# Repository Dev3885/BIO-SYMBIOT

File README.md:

# BIO SYMBIOT

**Bio-Resonant IoT Framework for Precision Microclimate Stabilization and Human-Plant Symbiosis**

An advanced IoT system that monitors and optimizes plant microclimates while mathematically quantifying the symbiotic relationship between tree biological resonance and human limbic well-being in a shared environment for regulation of the same towards overall health and tranquility.

---

Abstract

Inspired by research into plant communication networks, this project treats flora as an active, measurable node in a shared microclimate. We have built a mathematical proxy layer on top of real sensor data to test whether plant-state and human-comfort signals move together in a meaningful and mathematically honest way, proving that plants and humans react similarly in a given microclimate. And the results are amazing, we've achieved a **89.23%** of correlation between the plant's health and human limbic profile, when subjected to the exact same environment, with an alignment rate of **0.796**; which means that there is a 80% chance of predicting one variable, given the other variable. 
Next the project goes onto make use of this data to create a empathetic relationship between trees and humans. We have done that through actuation. 

The system validates a novel dual-bridge asymmetric weighting model for bio-symbiosis research, inspired by Peter Wohlleben’s **The Hidden Life of Trees**.

---

##  Key Features

- **Real-time Autonomous Irrigation** with manual override + 1-minute auto-timeout
- **Multi-sensor Microclimate Monitoring** (Soil Moisture, Ambient Light, Air Quality)
- **Local + Cloud Telemetry** (OLED display + Blynk IoT)
- **Advanced Noise Suppression** using FFT in MATLAB
- **Bio-Symbiosis Analytics** with Pearson correlation & linear regression (R² = 0.7962)
- **Robust Hardware Design** with optocoupler isolation, flyback diode, and star-ground topology
- **Professional PCB** designed in KiCad

---

##  Tech Stack

### Hardware
- **Microcontroller**: NodeMCU ESP8266
- **Sensors**: Capacitive Soil Moisture, BH1750 (Light), MQ-135 (Air Quality)
- **Display**: SSD1306 OLED (I2C)
- **Actuators**: 5V Relay + DC Water Pump
- **PCB**: Custom design in KiCad

### Software
- **Firmware**: Arduino (C++) with Blynk, non-blocking FSM
- **Analytics**: MATLAB (Serial parsing, FFT, regression, Shannon Entropy)
- **EDA**: KiCad

---

##  Results

- **Human-Tree Resonance Correlation**: **89.23%**
- **Predictive Model R²**: **0.7962**
- **System Stability Score** (Shannon Entropy): **27.94%**
- Successfully suppressed EMI and voltage sag issues
- Demonstrated clear asymmetric divergence validating the dual-bridge proxy model

---

##  Project Structure

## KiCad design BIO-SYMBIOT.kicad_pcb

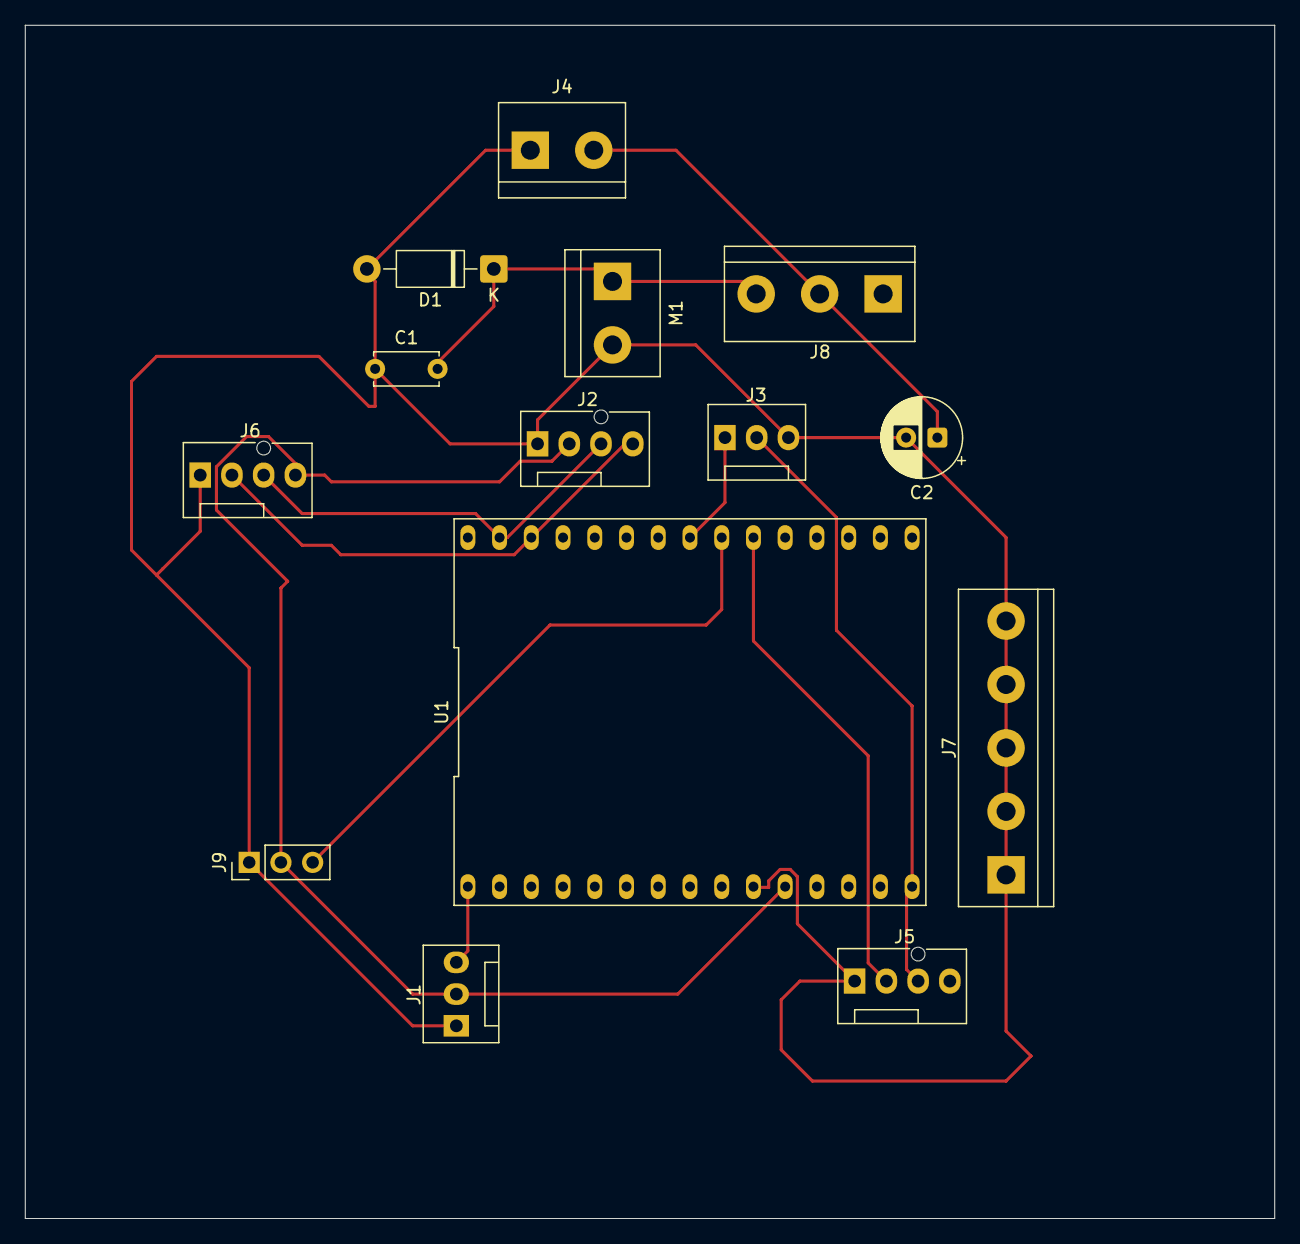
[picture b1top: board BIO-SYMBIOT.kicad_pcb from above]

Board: 2 copper layers, 100.0 x 95.5 mm, 14 parts (0 on the bottom side), 11 nets.

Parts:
C1: 0.1µF; C_Disc_D5.0mm_W2.5mm_P5.00mm
C2: 100µF; CP_Radial_D6.3mm_P2.50mm
D1: 1N4007; D_DO-41_SOD81_P10.16mm_Horizontal
J1: Soil Moisture Sensor; FanPinHeader_1x03_P2.54mm_Vertical
J2: SSD1306 OLED; FanPinHeader_1x04_P2.54mm_Vertical
J3: Rellay Module; FanPinHeader_1x03_P2.54mm_Vertical
J4: 5V Power Input; TerminalBlock_bornier-2_P5.08mm
J5: MQ135 Gas Sensor; FanPinHeader_1x04_P2.54mm_Vertical
J6: BH1750_LIGHT; FanPinHeader_1x04_P2.54mm_Vertical
J7: Screw_Terminal_01x05; TerminalBlock_bornier-5_P5.08mm
J8: Relay_Switch_Pins; TerminalBlock_bornier-3_P5.08mm
J9: TTP223 Touch Switch Module; PinHeader_1x03_P2.54mm_Vertical
M1: 5V Motor; TerminalBlock_bornier-2_P5.08mm
U1: NodeMCU1.0(ESP-12E); NodeMCU_LoLin_V3_Custom

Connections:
/5V: J3.2, J5.3, U1.15 (VIN)
/+3V3: J1.2, J2.2, J6.4, J9.2, U1.11 (3.3V)
/COM: C1.2, D1.1 (K), J8.3, M1.1 (+)
/GND: C1.1, C2.2, D1.2 (A), J1.1, J2.1, J3.3, J4.1, J5.1, J6.1, J7.1, J7.2, J7.3, J7.4, J7.5, J9.1, M1.2 (-), U1.10 (GND)
/I2C_SCL: J2.3, J6.3, U1.29 (D1(GPIO5))
/I2C_SDA: J2.4, J6.2, U1.28 (D2(GPIO4))
/MOISTURE_ANALOG: J1.3, U1.1 (A0(ADC0))
/MQ135_DIGITAL: J5.2, U1.21 (D7(GPIO13))
/RELAY_CTRL: J3.1, U1.23 (D5(GPIO14))
/TOUCH: J9.3, U1.22 (D6(GPIO12))
unnamed: C2.1, J4.2, J8.2
